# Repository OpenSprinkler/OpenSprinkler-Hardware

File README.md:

# OpenSprinkler-Hardware
OpenSprinkler Hardware and Enclosure files.
The .sch and .brd files are created in Eagle CAD.

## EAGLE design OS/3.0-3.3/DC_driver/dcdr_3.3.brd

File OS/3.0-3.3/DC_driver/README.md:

- Original DC driver board 3.0 uses PCF8574 (8-channel) IO expander with PNP transistor per channel.

- DC driver 3.1 (i.e. revision 1) uses a PCA9555 (16-channel) IO expander.

- DC driver 3.2 (i.e. revision 2) matches master version 3.2 with support for wired Ethernet module.

- DC driver 3.3 (i.e. revision 3) replaces the 7805 linear regulator with XL2001 switching regulator for higher power conversion efficiency, ideal when using the controller with wired Ethernet.

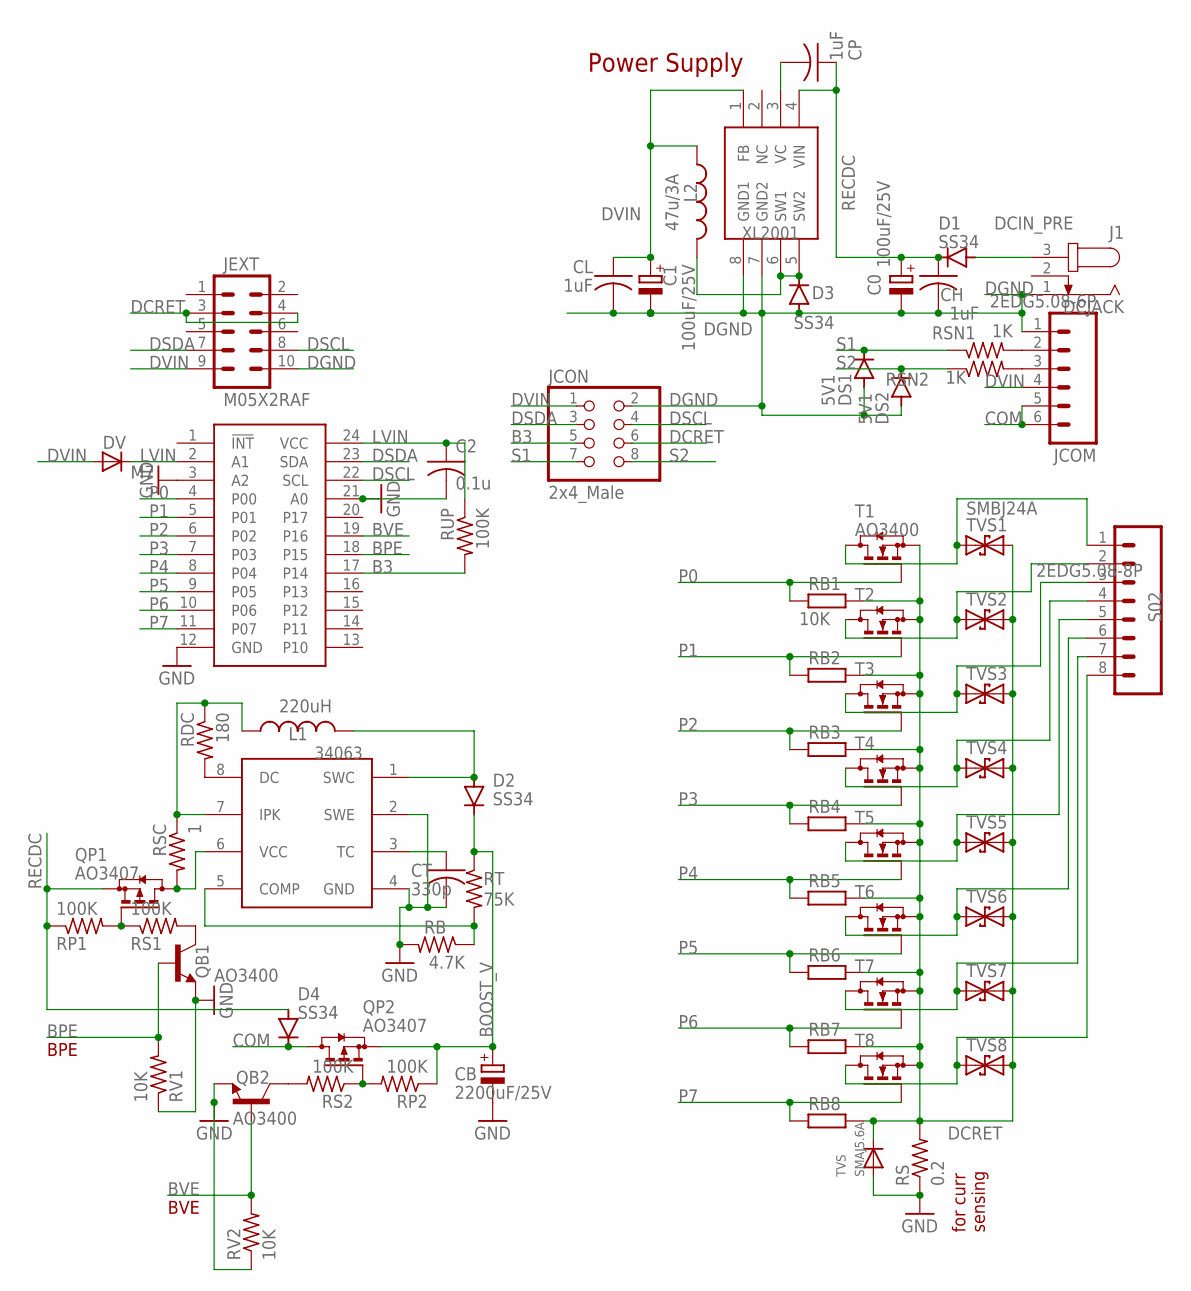
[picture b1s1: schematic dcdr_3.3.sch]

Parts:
34063: MC34063; SO08
C0, C1: 100uF/25V; E2-5
C2: 0.1u; C0603
CB: 2200uF/25V; E5-6
CH: 1uF; C0603K
CL: 1uF; C0603K
CP: 1uF; C0603K
CT: 330p; C0603K
D1, D2, D3, D4: SS34; SMB
DS1, DS2: 5V1; MINIMELF
DV: M7; SMA-DIODE
J1: DCJACK; SPC4077
JCOM: 2EDG5.08-6P; SCREWTERMINAL-5MM-6
JCON: 2x4_Male; 2X04
JEXT: M05X2RAF; 2X5-RAF
L1: 220uH; CR54
L2: 47u/3A; YT1014
PCA9555: PCA9555; TSSOP24
QB1, QB2: AO3400; SOT23-3
QP1, QP2: AO3407; SOT23
RB: 4.7K; R0603
RB1, RB2, RB3, RB4, RB5, RB6, RB7, RB8: 10K; R0603
RDC: 180; R0603
RP1, RP2: 100K; R0603
RS: 0.2; R2512
RS1, RS2: 100K; R0603
RSC: 1; R0603
RSN1, RSN2: 1K; R0603
RT: 75K; R0603
RUP: 100K; R0603
RV1, RV2: 10K; R0603
S02: 2EDG5.08-8P; SCREWTERMINAL-5MM-8
T1, T2, T3, T4, T5, T6, T7, T8: AO3400; SOT23
TVS: SMAJ5.6A; SMADIODE
TVS1, TVS2, TVS3, TVS4, TVS5, TVS6, TVS7, TVS8: SMBJ24A; SMB
XL2001: XL2001; SO08

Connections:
B3: JCON.5, PCA9555.17 (P14), RUP.2
BOOST_V: CB.+, D2.C, QP2.2 (S), RP2.1, RT.1
BPE: PCA9555.18 (P15), QB1.1 (B), RV1.2
BVE: PCA9555.19 (P16), QB2.1 (B), RV2.2
COM: D4.C, JCOM.5, JCOM.6, QP2.3 (D)
DCIN_PRE: D1.A, J1.3
DCRET: JCON.6, JEXT.3, JEXT.4, RB1.1, RB2.1, RB3.1, RB4.1, RB5.1, RB6.1, RB7.1, RB8.1, RS.2, T1.2 (S), T2.2 (S), T3.2 (S), T4.2 (S), T5.2 (S), T6.2 (S), T7.2 (S), T8.2 (S), TVS.C, TVS1.C, TVS2.C, TVS3.C, TVS4.C, TVS5.C, TVS6.C, TVS7.C, TVS8.C
DGND: 34063.2 (SWE), 34063.4 (GND), C0.-, C1.-, C2.2, CB.-, CH.2, CL.2, CT.2, D3.A, DS1.A, DS2.A, J1.1, JCOM.1, JCON.2, JEXT.10, PCA9555.3 (A2), PCA9555.12 (GND), PCA9555.21 (A0), QB1.2 (E), QB2.2 (E), RB.2, RS.1, RV1.1, RV2.1, TVS.A, XL2001.7 (GND2), XL2001.8 (GND1)
DSCL: JCON.4, JEXT.8, PCA9555.22 (SCL)
DSDA: JCON.3, JEXT.7, PCA9555.23 (SDA)
DVIN: C1.+, CL.1, DV.A, JCOM.4, JCON.1, JEXT.9, L2.P$2 (2), XL2001.1 (FB)
LVIN: C2.1, DV.C, PCA9555.2 (A1), PCA9555.24 (VCC), RUP.1
unnamed: 34063.1 (SWC), D2.A, L1.P$2 (2)
unnamed: JCOM.2, RSN1.2
unnamed: JCOM.3, RSN2.2
unnamed: D3.C, L2.P$1 (1), XL2001.5 (SW2), XL2001.6 (SW1)
unnamed: 34063.3 (TC), CT.1
unnamed: 34063.8 (DC), RDC.2
unnamed: CP.2, XL2001.3 (VC)
unnamed: 34063.7 (IPK), L1.P$1 (1), RDC.1, RSC.1
unnamed: 34063.6 (VCC), QP1.3 (D), RSC.2
unnamed: 34063.5 (COMP), RB.1, RT.2
unnamed: QP1.1 (G), RP1.2, RS1.1
unnamed: QB2.3 (C), RS2.2
unnamed: QB1.3 (C), RS1.2
unnamed: QP2.1 (G), RP2.2, RS2.1
unnamed: S02.1, T1.3 (D), TVS1.A
unnamed: S02.2, T2.3 (D), TVS2.A
unnamed: S02.3, T3.3 (D), TVS3.A
unnamed: S02.4, T4.3 (D), TVS4.A
unnamed: S02.5, T5.3 (D), TVS5.A
unnamed: S02.6, T6.3 (D), TVS6.A
unnamed: S02.7, T7.3 (D), TVS7.A
unnamed: S02.8, T8.3 (D), TVS8.A
P0: PCA9555.4 (P00), RB1.2, T1.1 (G)
P1: PCA9555.5 (P01), RB2.2, T2.1 (G)
P2: PCA9555.6 (P02), RB3.2, T3.1 (G)
P3: PCA9555.7 (P03), RB4.2, T4.1 (G)
P4: PCA9555.8 (P04), RB5.2, T5.1 (G)
P5: PCA9555.9 (P05), RB6.2, T6.1 (G)
P6: PCA9555.10 (P06), RB7.2, T7.1 (G)
P7: PCA9555.11 (P07), RB8.2, T8.1 (G)
RECDC: C0.+, CH.1, CP.1, D1.C, D4.A, QP1.2 (S), RP1.1, XL2001.4 (VIN)
S1: DS1.C, JCON.7, RSN1.1
S2: DS2.C, JCON.8, RSN2.1

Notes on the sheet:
BPE
BVE
for curr sensing
Power Supply

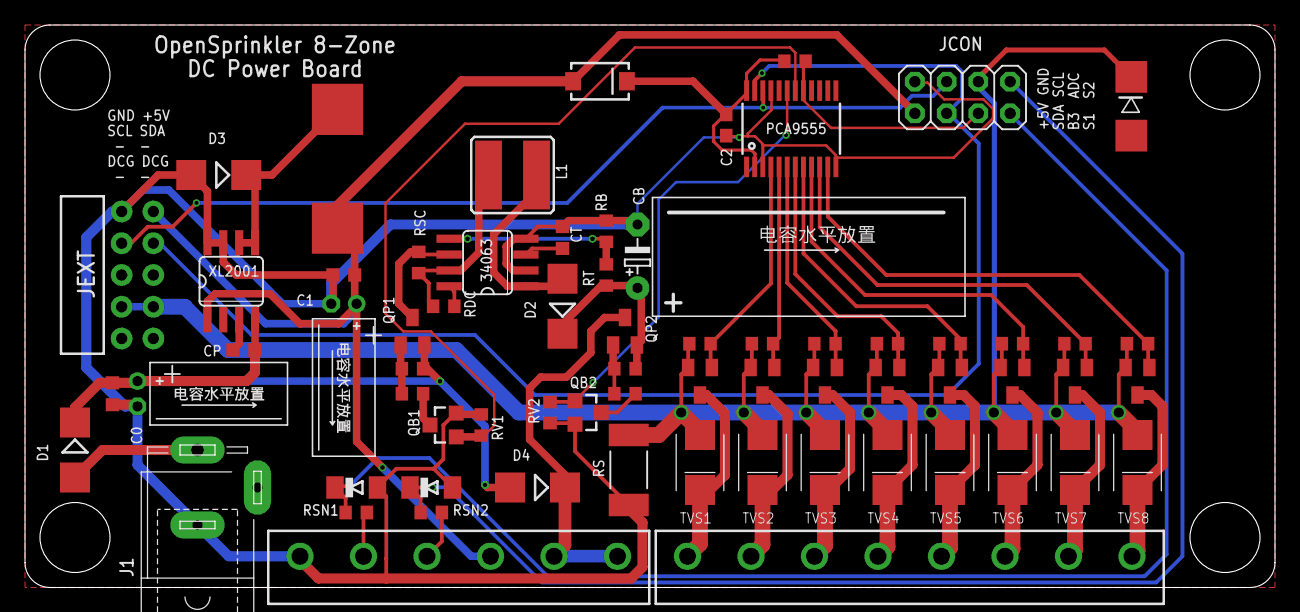
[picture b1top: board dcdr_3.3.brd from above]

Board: 2 copper layers, 100.0 x 45.0 mm, 68 parts (0 on the bottom side), 45 nets.

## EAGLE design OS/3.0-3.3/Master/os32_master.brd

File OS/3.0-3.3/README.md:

# OpenSprinkler 3.0-3.3
OpenSprinkler 3.0-3.3 used modularized design. It consists of two layers:
- Master Controller, based on ESP8266
- One of three types of drivers: AC, DC, or Latching

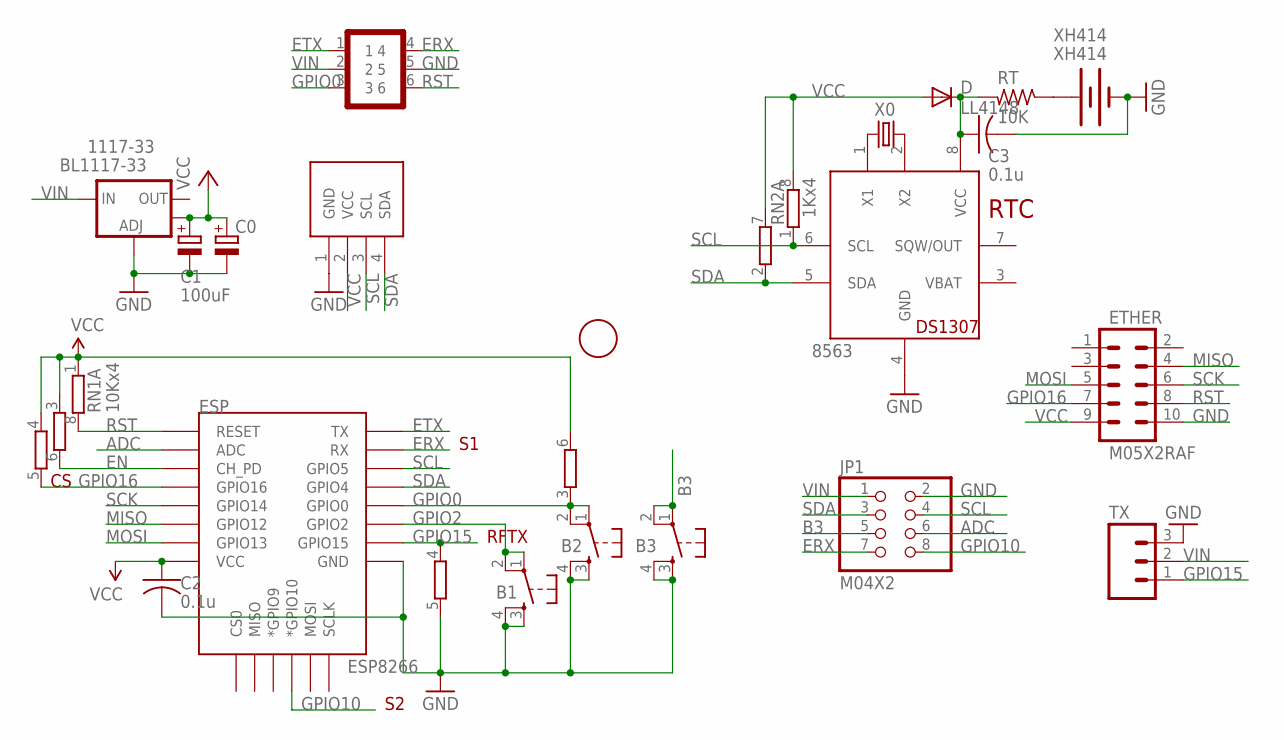
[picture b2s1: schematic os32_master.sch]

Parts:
1F: FIDUCIAL; FIDUCIAL_1MM
1117-33: BL1117-33; SOT223
8563: PCF8563; SO08
B1, B2, B3: SPST_TACTEVQQ2; EVQ-Q2
C0: CPOL-EUE2.5-5; E2,5-5
C1: 100uF; CT3528
C2, C3: 0.1u; C0603
D: LL4148; MINIMELF
ESP: ESP8266; ESP12E-SMD
ETHER: M05X2RAF; 2X5-RAF
JP1: M04X2; 2X04
LCD: SSD1306_OLED_I2CSMD3; SSD1306_OLED_I2C_SMD3
RN1: 10Kx4; EXB38V
RN2: 1Kx4; EXB38V
RT: 10K; R0603
TX: M03LOCK; 1X03_LOCK
U$3: GOLDFINGER_2X3
X0: 32.768kHz; MM20SS1
XH414: XH414; BATTCON_XH414

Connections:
ADC: ESP.ADC, JP1.6
B3: B3.1, B3.2, JP1.5
EN: ESP.CH_PD, RN1.6 (2)
ERX: ESP.RXD0 (RX), JP1.7, U$3.4
ETX: ESP.TXD0 (TX), U$3.1
GND: 1117-33.1 (ADJ), 8563.4 (GND), B1.3, B1.4, B2.3, B2.4, B3.3, B3.4, C0.-, C1.+ (-), C2.2, C3.2, ESP.GND, ETHER.10, JP1.2, LCD.1 (GND), RN2.5 (2), TX.3, U$3.5, XH414.P$1 (-)
GPIO0: B2.1, B2.2, ESP.GPIO0, RN2.3 (1), U$3.3
GPIO2: B1.1, B1.2, ESP.GPIO2
GPIO10: ESP.GPIO10 (*GPIO10), JP1.8
GPIO15: ESP.GPIO15, RN2.4 (1), TX.1
GPIO16: ESP.GPIO16, ETHER.7, RN1.5 (2)
MISO: ESP.GPIO12, ETHER.4
MOSI: ESP.GPIO13, ETHER.5
unnamed: 8563.1 (X1), X0.1
unnamed: 8563.8 (VCC), C3.1, D.C, RT.2
unnamed: 8563.2 (X2), X0.4 (2)
unnamed: RT.1, XH414.P$2 (+)
RST: ESP.RESET, ETHER.8, RN1.8 (2), U$3.6
SCK: ESP.GPIO14, ETHER.6
SCL: 8563.6 (SCL), ESP.GPIO5, JP1.4, LCD.3 (SCL), RN2.1
SDA: 8563.5 (SDA), ESP.GPIO4, JP1.3, LCD.4 (SDA), RN2.2 (1)
VBAT: 8563.3 (VBAT)
VCC: 1117-33.4 (OUT), C0.+, C1.- (+), C2.1, D.A, ESP.VCC, ETHER.9, LCD.2 (VCC), RN1.1, RN1.3 (1), RN1.4 (1), RN2.6 (2), RN2.7 (2), RN2.8 (2)
VIN: 1117-33.3 (IN), JP1.1, TX.2, U$3.2

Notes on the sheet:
RTC
RFTX

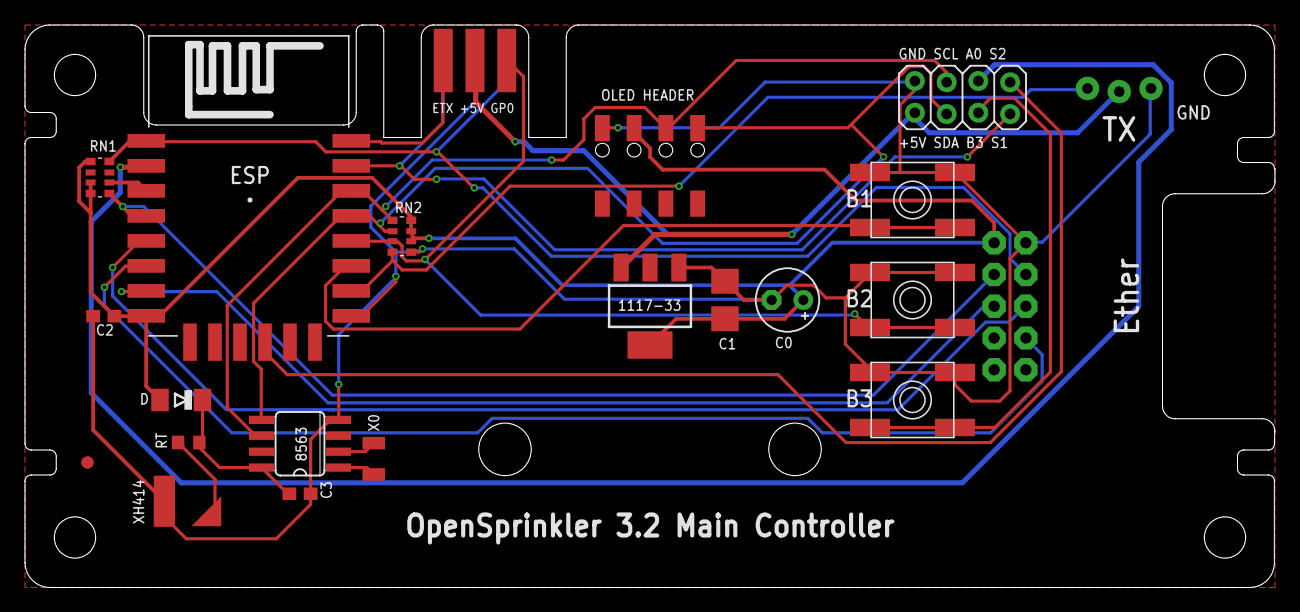
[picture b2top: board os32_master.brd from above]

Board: 2 copper layers, 100.0 x 45.0 mm, 22 parts (1 on the bottom side), 23 nets.

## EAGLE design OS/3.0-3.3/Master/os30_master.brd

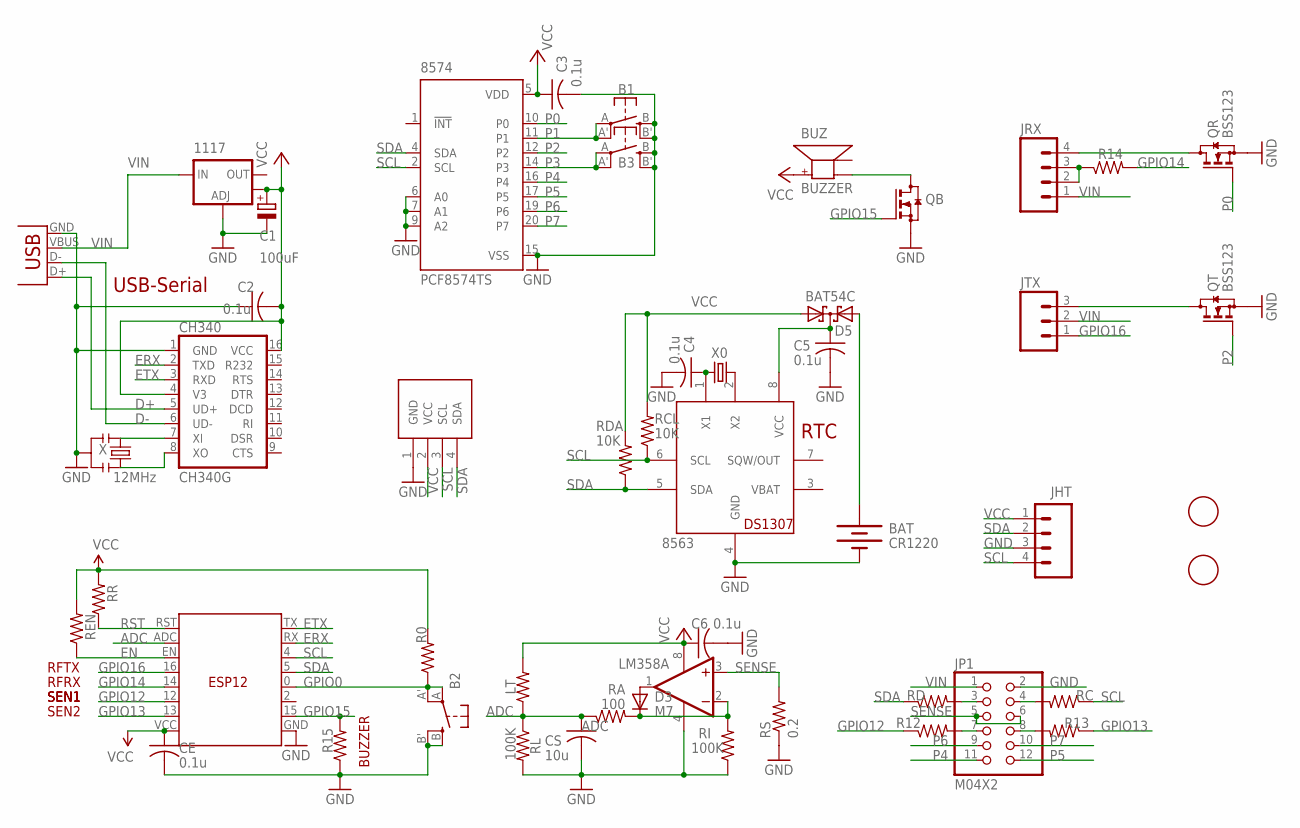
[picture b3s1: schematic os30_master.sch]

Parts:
1117: V_REG_LM1117SOT223; SOT223
8563: PCF8563; SO08
8574: PCF8574TS; SSOP20
B1, B2, B3: SPST_TACT-EVQQ2; EVQ-Q2
BAT: CR1220; BATTCON_12MM_SMT
BUZ: BUZZER; SMT-8585-BUZZER
C1: 100uF; PANASONIC_D
C2, C3, C4, C5, C6: 0.1u; C0603
CE: 0.1u; C0603
CH340: CH340G; SO16
CS: 10u; C0805K
D3: M7; DO-214AC
D5: BAT54C; SOT23
ESP: ESP; ESP12_WES
JHT: M04NARROW; 1X04-NARROW
JP1: M04X2; 2X06
JRX: M04PTH; 1X04
JTX: M03PTH; 1X03
LCD: SSD1306_OLED_I2CSMD3; SSD1306_OLED_I2C_SMD3
LM358: OP262D; SO08
LT: 100K; R1206
QB: AO3400; SOT23
QR: BSS123; SOT23
QT: BSS123; SOT23
R0: 10k; R0603
R12, R13: 4.7k; R0603
R14: 1K; R0603
R15: 10K; R0603
RA: 100; R0603
RC: 4.7k; R0603
RCL: 10K; R0603
RD: 330; R0603
RDA: 10K; R0603
REN: 10k; R0603
RI: 100K; R0603
RL: 100K; R0603
RR: 10k; R0603
RS: 0.2; R2512
U$1, U$2: FIDUCIAL; FIDUCIAL_1MM
USB: USBMICROB2; USB-MICROB2
X: 12MHz; RESONATOR-SMD
X0: 32.768kHz; MM20SS1

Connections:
ADC: CS.1, ESP.ADC, LT.1, RA.1, RL.1
D+: CH340.5 (UD+), USB.D+
D-: CH340.6 (UD-), USB.D-
EN: ESP.EN, REN.1
ERX: CH340.2 (TXD), ESP.RX
ETX: CH340.3 (RXD), ESP.TX
GND: 1117.1 (ADJ), 8563.4 (GND), 8574.6 (A0), 8574.7 (A1), 8574.9 (A2), 8574.15 (VSS), B1.B (S), B1.B' (S1), B2.B (S), B2.B' (S1), B3.B (S), B3.B' (S1), BAT.P$1 (-), C1.-, C2.1, C3.2, C4.2, C5.2, C6.2, CE.2, CH340.1 (GND), CS.2, ESP.GND, JHT.3, JP1.2, LCD.1 (GND), LM358.4 (V-), QB.2 (S), QR.2 (S), QT.2 (S), R15.1, RI.1, RL.2, RS.1, USB.GND, X.2
GPIO0: B2.A, B2.A' (P1), ESP.0 (G0), R0.1
GPIO12: ESP.12 (G12), R12.1
GPIO13: ESP.13 (G13), R13.1
GPIO14: ESP.14 (G14), R14.2
GPIO15: ESP.15 (G15), QB.1 (G), R15.2
GPIO16: ESP.16 (G16), JTX.1
unnamed: 8563.1 (X1), C4.1, X0.1
unnamed: BUZ.-, QB.3 (D)
unnamed: JP1.3, RD.2
unnamed: JP1.4, RC.2
unnamed: JP1.7, R12.2
unnamed: JP1.8, R13.2
unnamed: D3.C, LM358.2 (-IN), RA.2, RI.2
unnamed: 8563.8 (VCC), C5.1, D5.3 (CC)
unnamed: CH340.7 (XI), X.1
unnamed: JRX.2, JRX.3, R14.1
unnamed: JTX.3, QT.3 (D)
unnamed: JRX.4, QR.3 (D)
unnamed: 8563.2 (X2), X0.4 (2)
unnamed: BAT.P$2 (+), D5.2 (A2)
unnamed: CH340.8 (XO), X.3
unnamed: D3.A, LM358.1 (OUT)
P0: 8574.10 (P0), QR.1 (G)
P1: 8574.11 (P1), B1.A, B1.A' (P1)
P2: 8574.12 (P2), QT.1 (G)
P3: 8574.14 (P3), B3.A, B3.A' (P1)
P4: 8574.16 (P4), JP1.11
P5: 8574.17 (P5), JP1.12
P6: 8574.19 (P6), JP1.9
P7: 8574.20 (P7), JP1.10
RST: ESP.RST, RR.1
SCL: 8563.6 (SCL), 8574.2 (SCL), ESP.4 (G4), JHT.4, LCD.3 (SCL), RC.1, RCL.1
SDA: 8563.5 (SDA), 8574.4 (SDA), ESP.5 (G5), JHT.2, LCD.4 (SDA), RD.1, RDA.1
SENSE: JP1.5, JP1.6, LM358.3 (+IN), RS.2
VBAT: 8563.3 (VBAT)
VCC: 1117.4 (OUT), 8574.5 (VDD), BUZ.+, C1.+, C2.2, C3.1, C6.1, CE.1, CH340.4 (V3), CH340.16 (VCC), D5.1 (A1), ESP.VCC, JHT.1, LCD.2 (VCC), LM358.8 (V+), LT.2, R0.2, RCL.2, RDA.2, REN.2, RR.2
VIN: 1117.3 (IN), JP1.1, JRX.1, JTX.2, USB.VBUS

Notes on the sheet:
RTC
USB-Serial
SEN1
SEN2
RFRX
BUZZER
RFTX

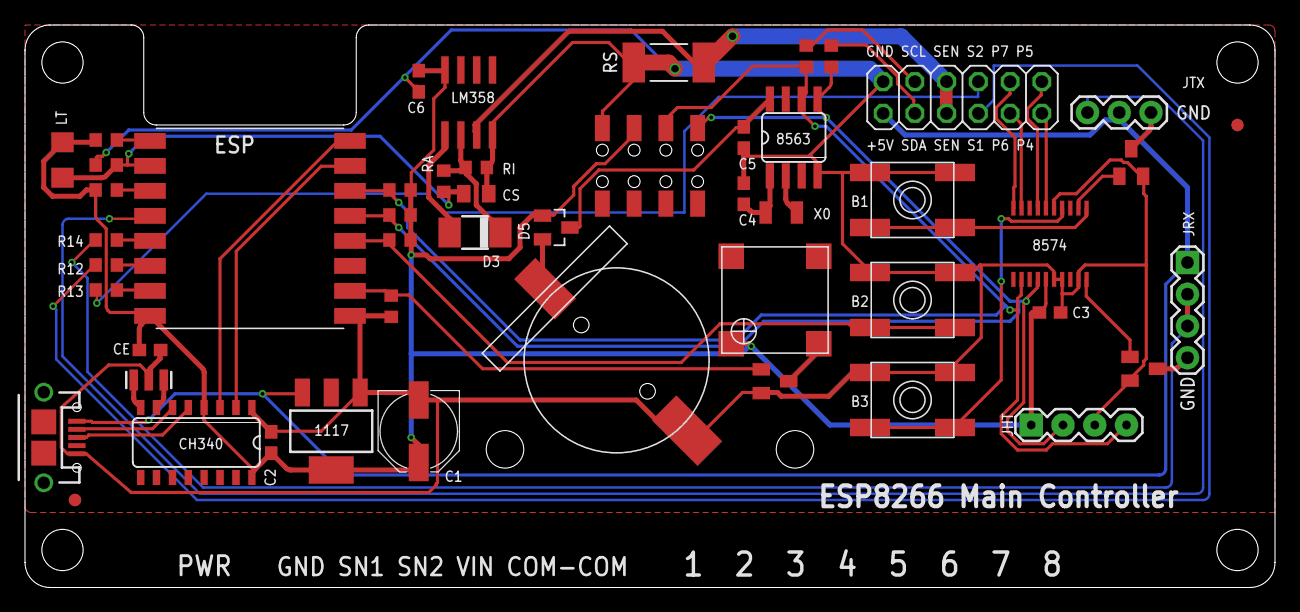
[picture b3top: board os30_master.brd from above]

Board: 2 copper layers, 100.0 x 45.0 mm, 50 parts (0 on the bottom side), 43 nets.

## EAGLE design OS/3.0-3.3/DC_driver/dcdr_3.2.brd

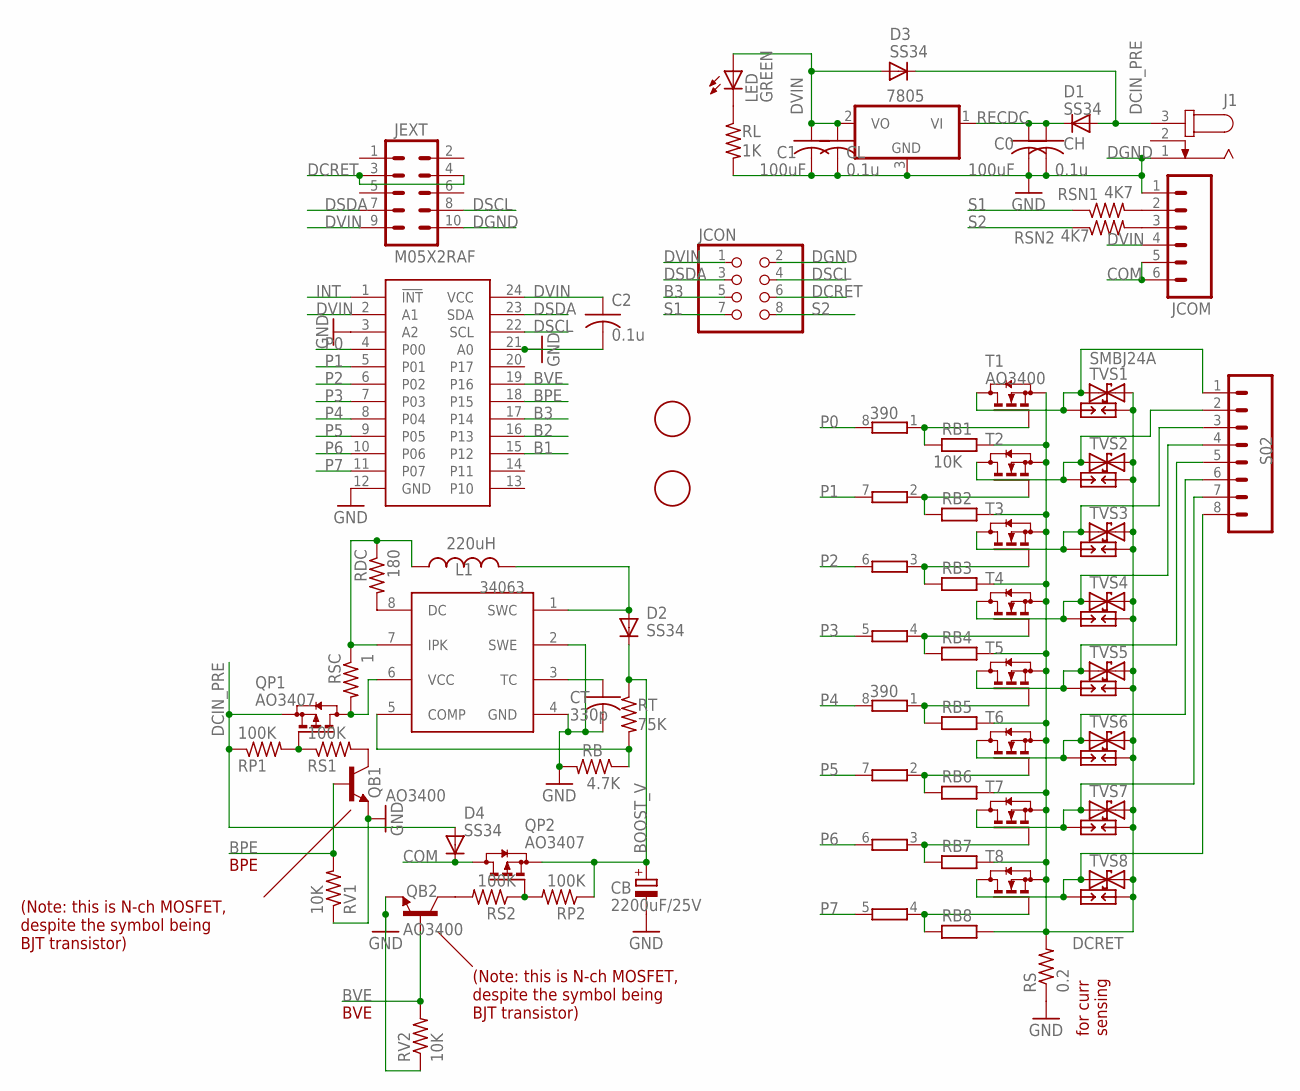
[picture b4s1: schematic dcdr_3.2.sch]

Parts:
7805: 7805DT; TO252
34063: MC34063; SO08
C0, C1: 100uF; C0805K
C2: 0.1u; C0603
CB: 2200uF/25V; E7,5-16
CH: 0.1u; C0603
CL: 0.1u; C0603
CT: 330p; C0603K
D1, D2, D3, D4: SS34; SMB
J1: JACK-PLUG0; SPC4077
JCOM: M065MM; SCREWTERMINAL-5MM-6
JCON: PINHD-2X4; 2X04
JEXT: M05X2RAF; 2X5-RAF
L1: 220uH; CR54
LED: GREEN; CHIPLED_0805
PCA9555: PCA9555; TSSOP24
QB1, QB2: AO3400; SOT23-3
QP1, QP2: AO3407; SOT23
RB: 4.7K; R0603
RB1, RB2, RB3, RB4, RB5, RB6, RB7, RB8: 10K; R0603
RDC: 180; R0603
RL: 1K; R0603
RN1, RN2: 390; EXB38V
RP1, RP2: 100K; R0603
RS: 0.2; R2512
RS1, RS2: 100K; R0603
RSC: 1; R0603
RSN1, RSN2: 4K7; R0603
RT: 75K; R0603
RV1, RV2: 10K; R0603
S02: M085MM-8; SCREWTERMINAL-5MM-8
SP1, SP2, SP3, SP4, SP5, SP6, SP7, SP8: PCB-SGAP
T1, T2, T3, T4, T5, T6, T7, T8: AO3400; SOT23
TVS1, TVS2, TVS3, TVS4, TVS5, TVS6, TVS7, TVS8: SMBJ24A; SMB
U$1, U$2: FIDUCIAL; FIDUCIAL_1MM

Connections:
B1: PCA9555.15 (P12)
B2: PCA9555.16 (P13)
B3: JCON.5, PCA9555.17 (P14)
BOOST_V: CB.+, D2.C, QP2.2 (S), RP2.1, RT.1
BPE: PCA9555.18 (P15), QB1.1 (B), RV1.2
BVE: PCA9555.19 (P16), QB2.1 (B), RV2.2
COM: D4.C, JCOM.5, JCOM.6, QP2.3 (D)
DCIN_PRE: D1.A, D3.C, D4.A, J1.3, QP1.2 (S), RP1.1
DCRET: JCON.6, JEXT.3, JEXT.4, RB1.1, RB2.1, RB3.1, RB4.1, RB5.1, RB6.1, RB7.1, RB8.1, RS.2, SP1.1, SP2.1, SP3.1, SP4.1, SP5.1, SP6.1, SP7.1, SP8.1, T1.2 (S), T2.2 (S), T3.2 (S), T4.2 (S), T5.2 (S), T6.2 (S), T7.2 (S), T8.2 (S), TVS1.C, TVS2.C, TVS3.C, TVS4.C, TVS5.C, TVS6.C, TVS7.C, TVS8.C
DGND: 7805.3 (GND), 34063.2 (SWE), 34063.4 (GND), C0.2, C1.2, C2.2, CB.-, CH.2, CL.2, CT.2, J1.1, JCOM.1, JCON.2, JEXT.10, PCA9555.3 (A2), PCA9555.12 (GND), PCA9555.21 (A0), QB1.2 (E), QB2.2 (E), RB.2, RL.2, RS.1, RV1.1, RV2.1
DSCL: JCON.4, JEXT.8, PCA9555.22 (SCL)
DSDA: JCON.3, JEXT.7, PCA9555.23 (SDA)
DVIN: 7805.2 (VO), C1.1, C2.1, CL.1, D3.A, JCOM.4, JCON.1, JEXT.9, LED.A, PCA9555.2 (A1), PCA9555.24 (VCC)
INT: PCA9555.1 (!INT)
unnamed: 34063.1 (SWC), D2.A, L1.P$2 (2)
unnamed: JCOM.2, RSN1.2
unnamed: JCOM.3, RSN2.2
unnamed: RB1.2, RN1.1, T1.1 (G)
unnamed: RB2.2, RN1.2 (1), T2.1 (G)
unnamed: RB3.2, RN1.3 (1), T3.1 (G)
unnamed: RB4.2, RN1.4 (1), T4.1 (G)
unnamed: 34063.3 (TC), CT.1
unnamed: RB5.2, RN2.1, T5.1 (G)
unnamed: RB6.2, RN2.2 (1), T6.1 (G)
unnamed: RB7.2, RN2.3 (1), T7.1 (G)
unnamed: RB8.2, RN2.4 (1), T8.1 (G)
unnamed: 34063.8 (DC), RDC.2
unnamed: 34063.7 (IPK), L1.P$1 (1), RDC.1, RSC.1
unnamed: 34063.6 (VCC), QP1.3 (D), RSC.2
unnamed: LED.C, RL.1
unnamed: 34063.5 (COMP), RB.1, RT.2
unnamed: QP1.1 (G), RP1.2, RS1.1
unnamed: QB2.3 (C), RS2.2
unnamed: QB1.3 (C), RS1.2
unnamed: QP2.1 (G), RP2.2, RS2.1
unnamed: S02.1, SP1.2, T1.3 (D), TVS1.A
unnamed: S02.2, SP2.2, T2.3 (D), TVS2.A
unnamed: S02.3, SP3.2, T3.3 (D), TVS3.A
unnamed: S02.4, SP4.2, T4.3 (D), TVS4.A
unnamed: S02.5, SP5.2, T5.3 (D), TVS5.A
unnamed: S02.6, SP6.2, T6.3 (D), TVS6.A
unnamed: S02.7, SP7.2, T7.3 (D), TVS7.A
unnamed: S02.8, SP8.2, T8.3 (D), TVS8.A
P0: PCA9555.4 (P00), RN1.8 (2)
P1: PCA9555.5 (P01), RN1.7 (2)
P2: PCA9555.6 (P02), RN1.6 (2)
P3: PCA9555.7 (P03), RN1.5 (2)
P4: PCA9555.8 (P04), RN2.8 (2)
P5: PCA9555.9 (P05), RN2.7 (2)
P6: PCA9555.10 (P06), RN2.6 (2)
P7: PCA9555.11 (P07), RN2.5 (2)
RECDC: 7805.1 (VI), C0.1, CH.1, D1.C
S1: JCON.7, RSN1.1
S2: JCON.8, RSN2.1

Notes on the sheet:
BPE
BVE
for curr sensing
(Note: this is N-ch MOSFET, despite the symbol being BJT transistor)

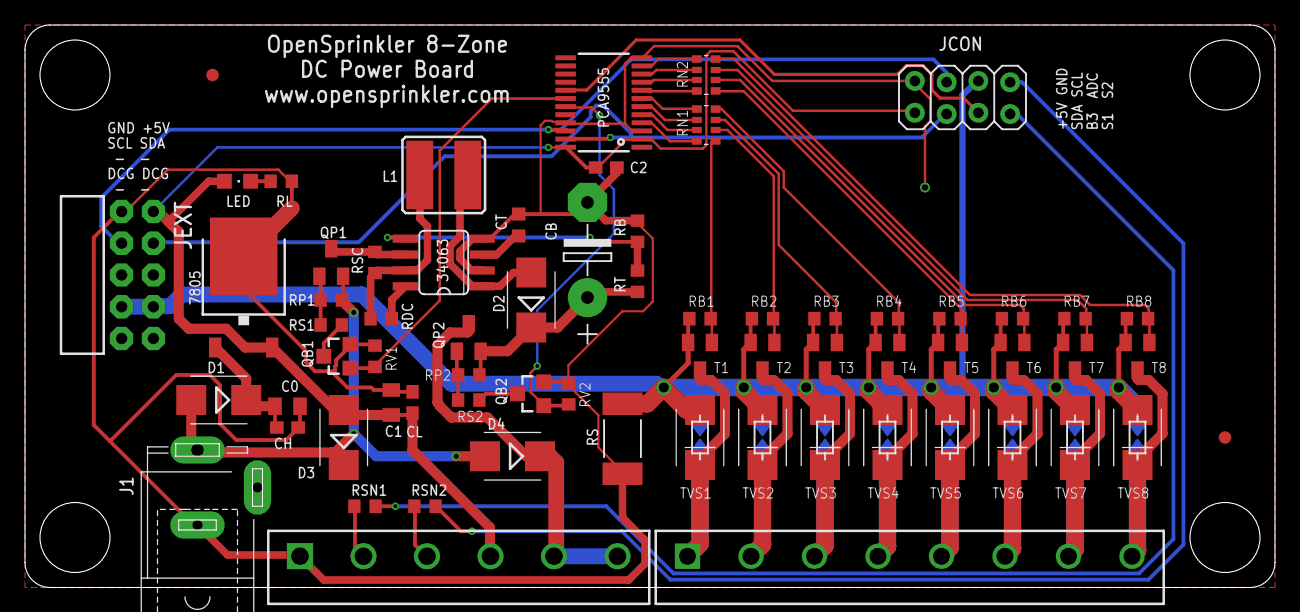
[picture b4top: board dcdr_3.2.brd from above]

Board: 2 copper layers, 100.0 x 45.0 mm, 75 parts (0 on the bottom side), 51 nets.

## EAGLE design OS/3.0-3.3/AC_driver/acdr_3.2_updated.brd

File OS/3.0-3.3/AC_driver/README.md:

- Original AC driver board 3.0 uses PCF8574 (8-channel) IO expander with PNP transistor per channel to drive triac.

- AC driver 3.1 (i.e. revision 1) uses a PCA9555 (16-channel) IO expander.

- AC driver 3.2 (i.e. revision 2) matches master version 3.2 with support for wired Ethernet module.

- AC driver 3.2-updated (revision 3) adds a diode drop on PCA9555's VIN pin for more reliable interface with ESP8266's 3.3V logic.

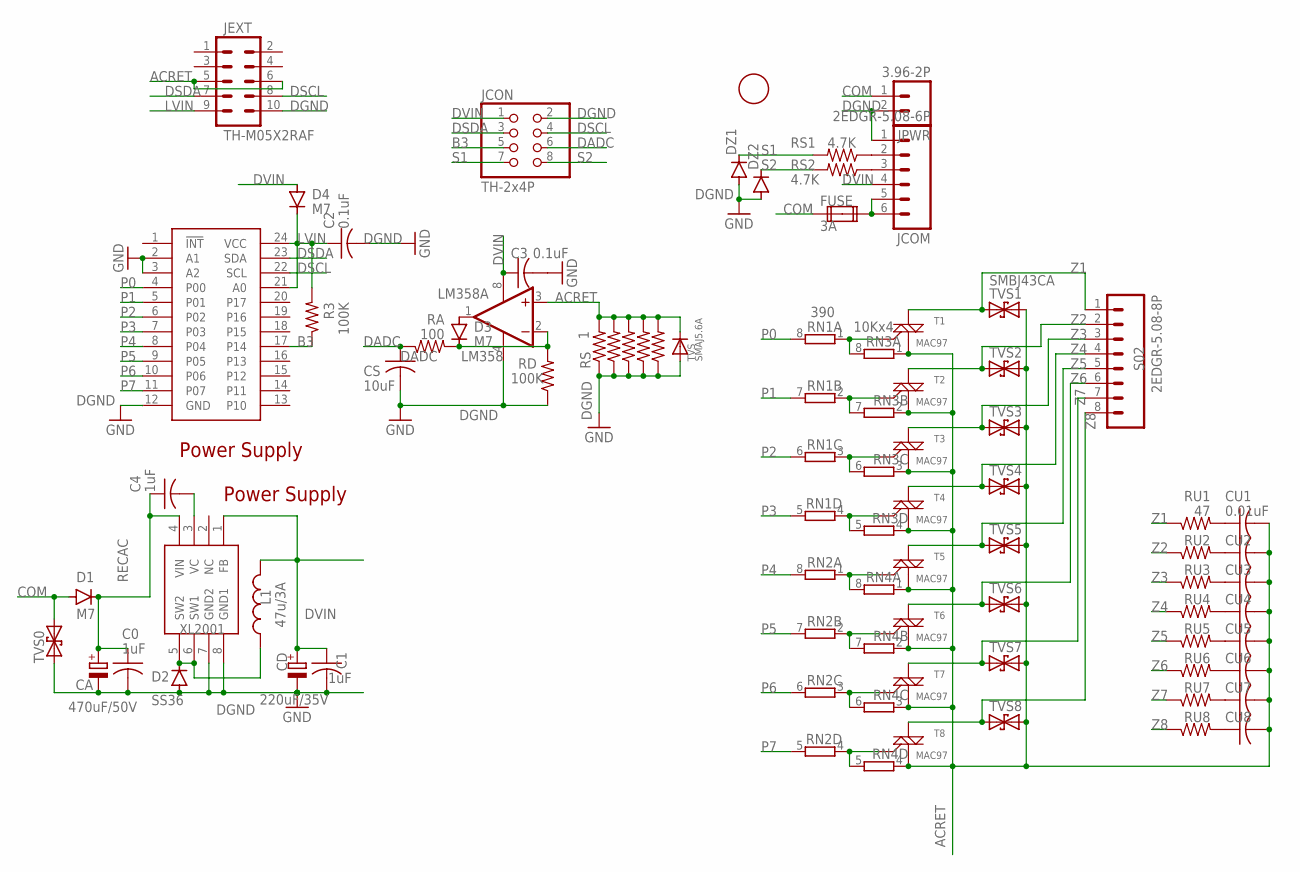
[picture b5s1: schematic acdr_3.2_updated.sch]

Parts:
1F: FIDUCIAL; FIDUCIAL_1MM
C0, C1, C4: 1uF; C0603K
C2, C3: 0.1uF; C0603K
CA: 470uF/50V; E5-10,5
CD: 220uF/35V; E3,5-8
CS: 10uF; C0805K
CU1, CU2, CU3, CU4, CU5, CU6, CU7, CU8: 0.01uF; C0603K
D1, D3, D4: M7; DO214AC
D2: SS36; SMB
DZ1, DZ2: ZMM5V1; MINIMELF
FUSE: 3A; FUSE1
JCOM: 2EDGR-5.08-6P; SCREWTERMINAL-5MM-6
JCON: TH-2x4P; 2X04
JEXT: TH-M05X2RAF; 2X5-RAF
JPWR: 3.96-2P; SCREWTERMINAL-4MM-2-X
L1: 47u/3A; YT1014
LM358: LM358; SO08
PCA9555: PCA9555; TSSOP24
R3: 100K; R0603
RA: 100; R0603
RD: 100K; R0603
RN1, RN2: 390; EXB38V
RN3, RN4: 10Kx4; EXB38V
RS: 1; R2512
RS1, RS2: 4.7K; R0603
RSA: 1; R2512
RSB: 1; R2512
RSC: 1; R2512
RSD: 1; R2512
RU1, RU2, RU3, RU4, RU5, RU6, RU7, RU8: 47; R0603
S02: 2EDGR-5.08-8P; SCREWTERMINAL-5MM-8
T1, T2, T3, T4, T5, T6, T7, T8: MAC97; TO-92-STRAIGHT
TVS: SMAJ5.6A; SMADIODE
TVS0, TVS1, TVS2, TVS3, TVS4, TVS5, TVS6, TVS7, TVS8: SMBJ43CA; SMB
XL2001: XL2001; SO08

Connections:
ACRET: CU1.2, CU2.2, CU3.2, CU4.2, CU5.2, CU6.2, CU7.2, CU8.2, JEXT.5, JEXT.6, LM358.3 (+IN), RN3.1, RN3.2 (1), RN3.3 (1), RN3.4 (1), RN4.1, RN4.2 (1), RN4.3 (1), RN4.4 (1), RS.2, RSA.2, RSB.2, RSC.2, RSD.2, T1.1 (M1), T2.1 (M1), T3.1 (M1), T4.1 (M1), T5.1 (M1), T6.1 (M1), T7.1 (M1), T8.1 (M1), TVS.C, TVS1.C, TVS2.C, TVS3.C, TVS4.C, TVS5.C, TVS6.C, TVS7.C, TVS8.C
B3: JCON.5, PCA9555.17 (P14), R3.1
COM: D1.A, FUSE.1A, JPWR.1, TVS0.C
DADC: CS.1, JCON.6, RA.1
DGND: C0.2, C1.2, C2.2, C3.2, CA.-, CD.-, CS.2, D2.A, DZ1.A, DZ2.A, JCOM.1, JCON.2, JEXT.10, JPWR.2, LM358.4 (V-), PCA9555.2 (A1), PCA9555.3 (A2), PCA9555.12 (GND), RD.1, RS.1, RSA.1, RSB.1, RSC.1, RSD.1, TVS.A, TVS0.A, XL2001.7 (GND2), XL2001.8 (GND1)
DSCL: JCON.4, JEXT.8, PCA9555.22 (SCL)
DSDA: JCON.3, JEXT.7, PCA9555.23 (SDA)
DVIN: C1.1, C3.1, CD.+, D4.A, JCOM.4, JCON.1, L1.P$2 (2), LM358.8 (V+), XL2001.1 (FB)
FCOM: FUSE.2A, JCOM.5, JCOM.6
LVIN: C2.1, D4.C, JEXT.9, PCA9555.21 (A0), PCA9555.24 (VCC), R3.2
unnamed: JCOM.2, RS1.1
unnamed: CU1.1, RU1.2
unnamed: JCOM.3, RS2.1
unnamed: CU2.1, RU2.2
unnamed: CU3.1, RU3.2
unnamed: CU4.1, RU4.2
unnamed: D3.C, LM358.2 (-IN), RA.2, RD.2
unnamed: RN1.1, RN3.8 (2), T1.2 (G)
unnamed: RN1.2 (1), RN3.7 (2), T2.2 (G)
unnamed: CU5.1, RU5.2
unnamed: CU6.1, RU6.2
unnamed: CU7.1, RU7.2
unnamed: CU8.1, RU8.2
unnamed: RN1.3 (1), RN3.6 (2), T3.2 (G)
unnamed: RN1.4 (1), RN3.5 (2), T4.2 (G)
unnamed: RN2.1, RN4.8 (2), T5.2 (G)
unnamed: RN2.2 (1), RN4.7 (2), T6.2 (G)
unnamed: RN2.3 (1), RN4.6 (2), T7.2 (G)
unnamed: RN2.4 (1), RN4.5 (2), T8.2 (G)
unnamed: D2.C, L1.P$1 (1), XL2001.5 (SW2), XL2001.6 (SW1)
unnamed: C4.2, XL2001.3 (VC)
unnamed: D3.A, LM358.1 (OUT)
P0: PCA9555.4 (P00), RN1.8 (2)
P1: PCA9555.5 (P01), RN1.7 (2)
P2: PCA9555.6 (P02), RN1.6 (2)
P3: PCA9555.7 (P03), RN1.5 (2)
P4: PCA9555.8 (P04), RN2.8 (2)
P5: PCA9555.9 (P05), RN2.7 (2)
P6: PCA9555.10 (P06), RN2.6 (2)
P7: PCA9555.11 (P07), RN2.5 (2)
RECAC: C0.1, C4.1, CA.+, D1.C, XL2001.4 (VIN)
S1: DZ1.C, JCON.7, RS1.2
S2: DZ2.C, JCON.8, RS2.2
Z1: RU1.1, S02.1, T1.3 (M2), TVS1.A
Z2: RU2.1, S02.2, T2.3 (M2), TVS2.A
Z3: RU3.1, S02.3, T3.3 (M2), TVS3.A
Z4: RU4.1, S02.4, T4.3 (M2), TVS4.A
Z5: RU5.1, S02.5, T5.3 (M2), TVS5.A
Z6: RU6.1, S02.6, T6.3 (M2), TVS6.A
Z7: RU7.1, S02.7, T7.3 (M2), TVS7.A
Z8: RU8.1, S02.8, T8.3 (M2), TVS8.A

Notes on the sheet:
Power Supply

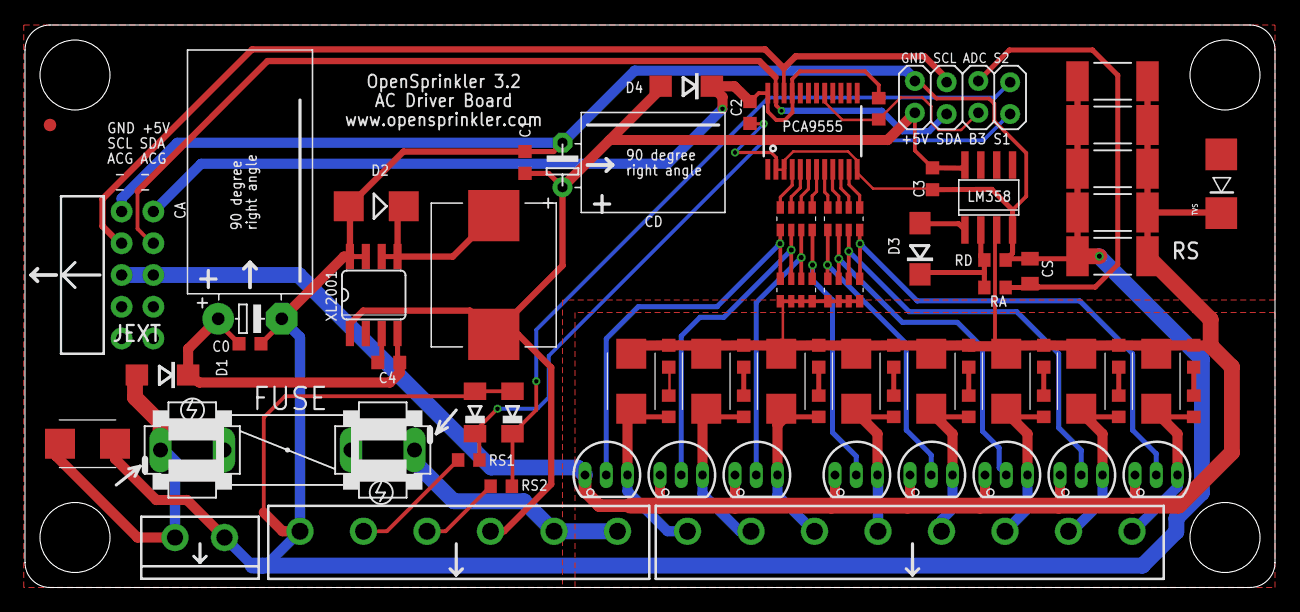
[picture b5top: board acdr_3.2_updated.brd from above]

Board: 2 copper layers, 100.0 x 45.0 mm, 73 parts (0 on the bottom side), 51 nets.

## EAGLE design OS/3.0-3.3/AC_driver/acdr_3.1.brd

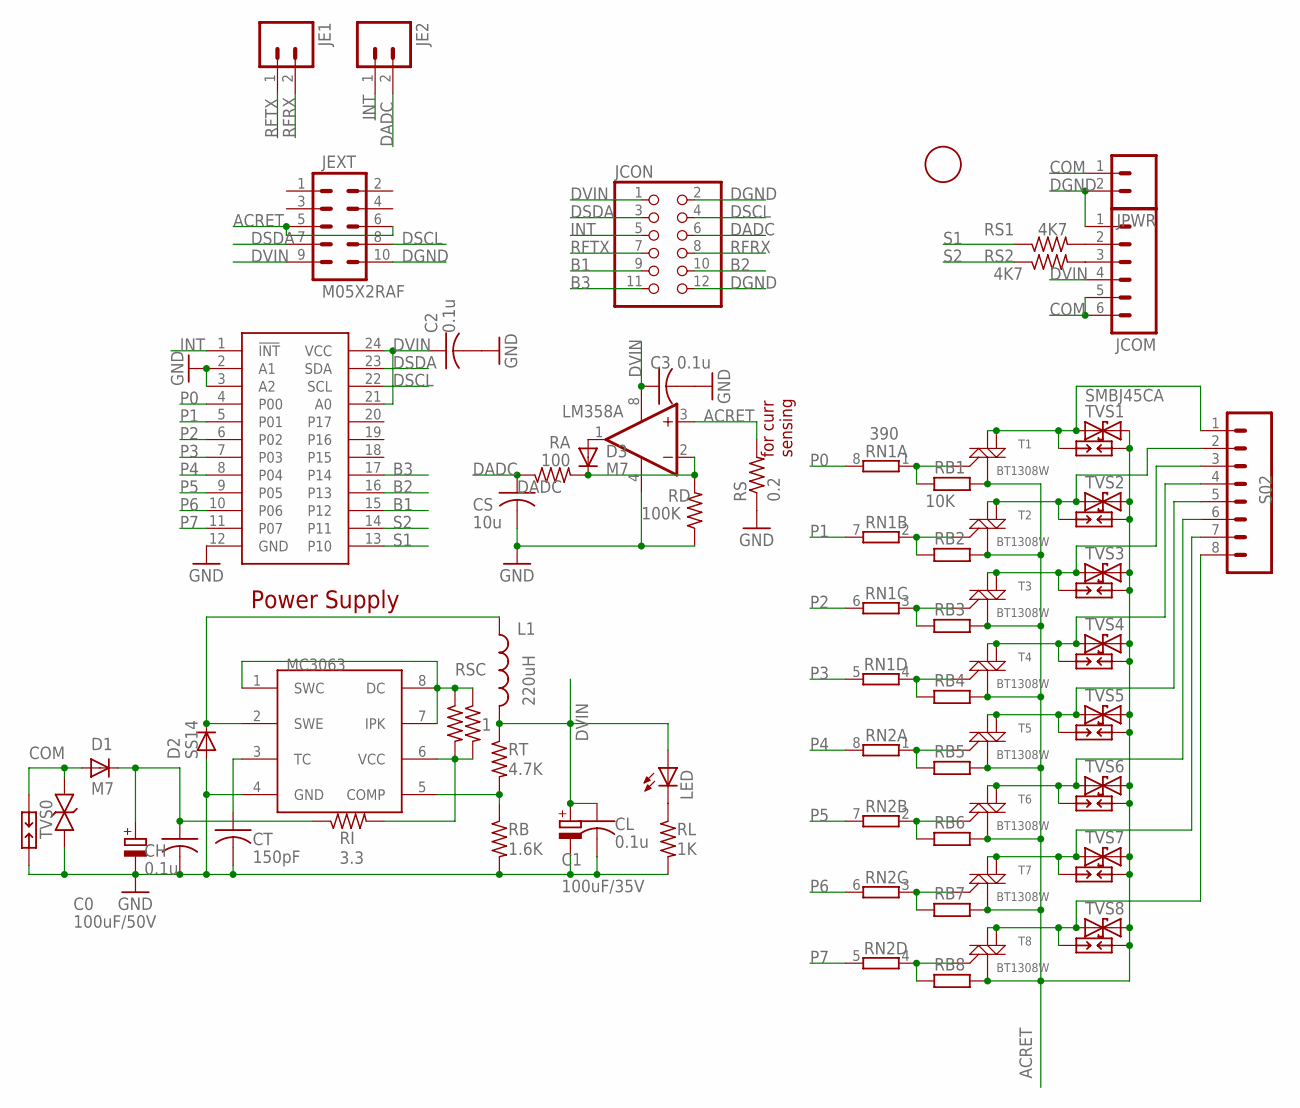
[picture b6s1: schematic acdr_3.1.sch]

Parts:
1F: FIDUCIAL; FIDUCIAL_1MM
C0: 100uF/50V; PANASONIC_E
C1: 100uF/35V; PANASONIC_D
C2, C3: 0.1u; C0603
CH: 0.1u; C0603
CL: 0.1u; C0603
CS: 10u; C0805K
CT: 150pF; C0603K
D1, D3: M7; DO-214AC
D2: SS14; DO-214AC
JCOM: M065MM; SCREWTERMINAL-5MM-6
JCON: PINHD-2X6; 2X06
JE1, JE2: M02PTH; 1X02
JEXT: M05X2RAF; 2X5-RAF
JPWR: M024MM-X; SCREWTERMINAL-4MM-2-X
L1: 220uH; SRU1038
LED: LEDCHIPLED_0805; CHIPLED_0805
LM358: OP262D; SO08
MC3063: MC34063; SO08
PCA9555: PCA9555; TSSOP24
RA: 100; R0603
RB: 1.6K; R0603
RB1, RB2, RB3, RB4, RB5, RB6, RB7, RB8: 10K; R0603
RD: 100K; R0603
RI: 3.3; R2010
RL: 1K; R0603
RN1, RN2: 390; EXB38V
RS: 0.2; R2512
RS1, RS2: 4K7; R0603
RSC, RSC1: 1; R0805
RT: 4.7K; R0603
S02: M085MM-8; SCREWTERMINAL-5MM-8
SP0, SP1, SP2, SP3, SP4, SP5, SP6, SP7, SP8: PCB-SGAP
T1, T2, T3, T4, T5, T6, T7, T8: BT1308W; SOT223
TVS0, TVS1, TVS2, TVS3, TVS4, TVS5, TVS6, TVS7, TVS8: SMBJ45CA; SMB

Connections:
ACRET: JEXT.5, JEXT.6, LM358.3 (+IN), RB1.1, RB2.1, RB3.1, RB4.1, RB5.1, RB6.1, RB7.1, RB8.1, RS.2, SP1.1, SP2.1, SP3.1, SP4.1, SP5.1, SP6.1, SP7.1, SP8.1, T1.1 (M1), T2.1 (M1), T3.1 (M1), T4.1 (M1), T5.1 (M1), T6.1 (M1), T7.1 (M1), T8.1 (M1), TVS1.C, TVS2.C, TVS3.C, TVS4.C, TVS5.C, TVS6.C, TVS7.C, TVS8.C
B1: JCON.9, PCA9555.15 (P12)
B2: JCON.10, PCA9555.16 (P13)
B3: JCON.11, PCA9555.17 (P14)
COM: D1.A, JCOM.5, JCOM.6, JPWR.1, SP0.1, TVS0.C
DADC: CS.1, JCON.6, JE2.2, RA.1
DGND: C0.-, C1.-, C2.2, C3.2, CH.2, CL.2, CS.2, CT.2, D2.A, JCOM.1, JCON.2, JCON.12, JEXT.10, JPWR.2, LM358.4 (V-), MC3063.4 (GND), PCA9555.2 (A1), PCA9555.3 (A2), PCA9555.12 (GND), RB.2, RD.1, RL.2, RS.1, SP0.2, TVS0.A
DSCL: JCON.4, JEXT.8, PCA9555.22 (SCL)
DSDA: JCON.3, JEXT.7, PCA9555.23 (SDA)
DVIN: C1.+, C2.1, C3.1, CL.1, JCOM.4, JCON.1, JEXT.9, L1.2, LED.A, LM358.8 (V+), PCA9555.21 (A0), PCA9555.24 (VCC), RT.1
INT: JCON.5, JE2.1, PCA9555.1 (!INT)
unnamed: MC3063.1 (SWC), MC3063.7 (IPK), MC3063.8 (DC), RSC.1, RSC1.1
unnamed: JCOM.2, RS1.2
unnamed: JCOM.3, RS2.2
unnamed: D3.C, LM358.2 (-IN), RA.2, RD.2
unnamed: RB1.2, RN1.1, T1.3 (G)
unnamed: RB2.2, RN1.2 (1), T2.3 (G)
unnamed: RB3.2, RN1.3 (1), T3.3 (G)
unnamed: RB4.2, RN1.4 (1), T4.3 (G)
unnamed: D2.C, L1.1, MC3063.2 (SWE)
unnamed: RB5.2, RN2.1, T5.3 (G)
unnamed: RB6.2, RN2.2 (1), T6.3 (G)
unnamed: RB7.2, RN2.3 (1), T7.3 (G)
unnamed: RB8.2, RN2.4 (1), T8.3 (G)
unnamed: CT.1, MC3063.3 (TC)
unnamed: MC3063.5 (COMP), RB.1, RT.2
unnamed: MC3063.6 (VCC), RI.2, RSC.2, RSC1.2
unnamed: LED.C, RL.1
unnamed: D3.A, LM358.1 (OUT)
unnamed: S02.1, SP1.2, T1.2 (M2), T1.4 (M2-4), TVS1.A
unnamed: S02.2, SP2.2, T2.2 (M2), T2.4 (M2-4), TVS2.A
unnamed: S02.3, SP3.2, T3.2 (M2), T3.4 (M2-4), TVS3.A
unnamed: S02.4, SP4.2, T4.2 (M2), T4.4 (M2-4), TVS4.A
unnamed: S02.5, SP5.2, T5.2 (M2), T5.4 (M2-4), TVS5.A
unnamed: S02.6, SP6.2, T6.2 (M2), T6.4 (M2-4), TVS6.A
unnamed: S02.7, SP7.2, T7.2 (M2), T7.4 (M2-4), TVS7.A
unnamed: S02.8, SP8.2, T8.2 (M2), T8.4 (M2-4), TVS8.A
P0: PCA9555.4 (P00), RN1.8 (2)
P1: PCA9555.5 (P01), RN1.7 (2)
P2: PCA9555.6 (P02), RN1.6 (2)
P3: PCA9555.7 (P03), RN1.5 (2)
P4: PCA9555.8 (P04), RN2.8 (2)
P5: PCA9555.9 (P05), RN2.7 (2)
P6: PCA9555.10 (P06), RN2.6 (2)
P7: PCA9555.11 (P07), RN2.5 (2)
RECAC: C0.+, CH.1, D1.C, RI.1
RFRX: JCON.8, JE1.2
RFTX: JCON.7, JE1.1
S1: PCA9555.13 (P10), RS1.1
S2: PCA9555.14 (P11), RS2.1

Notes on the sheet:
Power Supply
for curr sensing

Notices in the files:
parts and their libraries:
SparkFunNew: Licensing: CC v3.0 Share-Alike You are welcome to use this library for commercial purposes.
